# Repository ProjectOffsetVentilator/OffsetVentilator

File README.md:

# OffsetVentilator
Main code and documentation repository for the Helpful Engineering Offset Ventilator project.

## Google drive files
Original Proposal https://docs.google.com/document/d/1oH8tw4RyOXmuNEdUx4EB1WGNugmwalZ1q0ezBaePJMA/edit?usp=sharing

Intro Document https://docs.google.com/document/d/1AArDUr8NLNWiVp7JXv_tODoiIWyCNlN2cYjHagHkWg8/edit?usp=sharing

Rapidly Manufactured Ventilator Specs (MHRA) https://drive.google.com/file/d/1wRC2XBbxR0HcKKCPTSRZzICJgym3Go8j/view?usp=sharing

Minimal viable product https://drive.google.com/file/d/13SMGtRrQCkC2kCIZivcb2gAX9uvTnBLK/view?usp=sharing

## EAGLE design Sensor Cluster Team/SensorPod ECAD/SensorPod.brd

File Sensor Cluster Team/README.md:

# Sensor Cluster Team Readme

## Team Google files
Sensor spec sheet https://docs.google.com/spreadsheets/d/1ZPNHejLOZxX_iVy-8t1VuLuAKOtTS-A7I4RntlRBN0Y/edit?usp=sharing

## Useful links and resources
MVP specs https://drive.google.com/file/d/13SMGtRrQCkC2kCIZivcb2gAX9uvTnBLK/view?usp=sharing

Rapidly Manufactured Ventilator System specs (MHRA) https://drive.google.com/file/d/1wRC2XBbxR0HcKKCPTSRZzICJgym3Go8j/view?usp=sharing

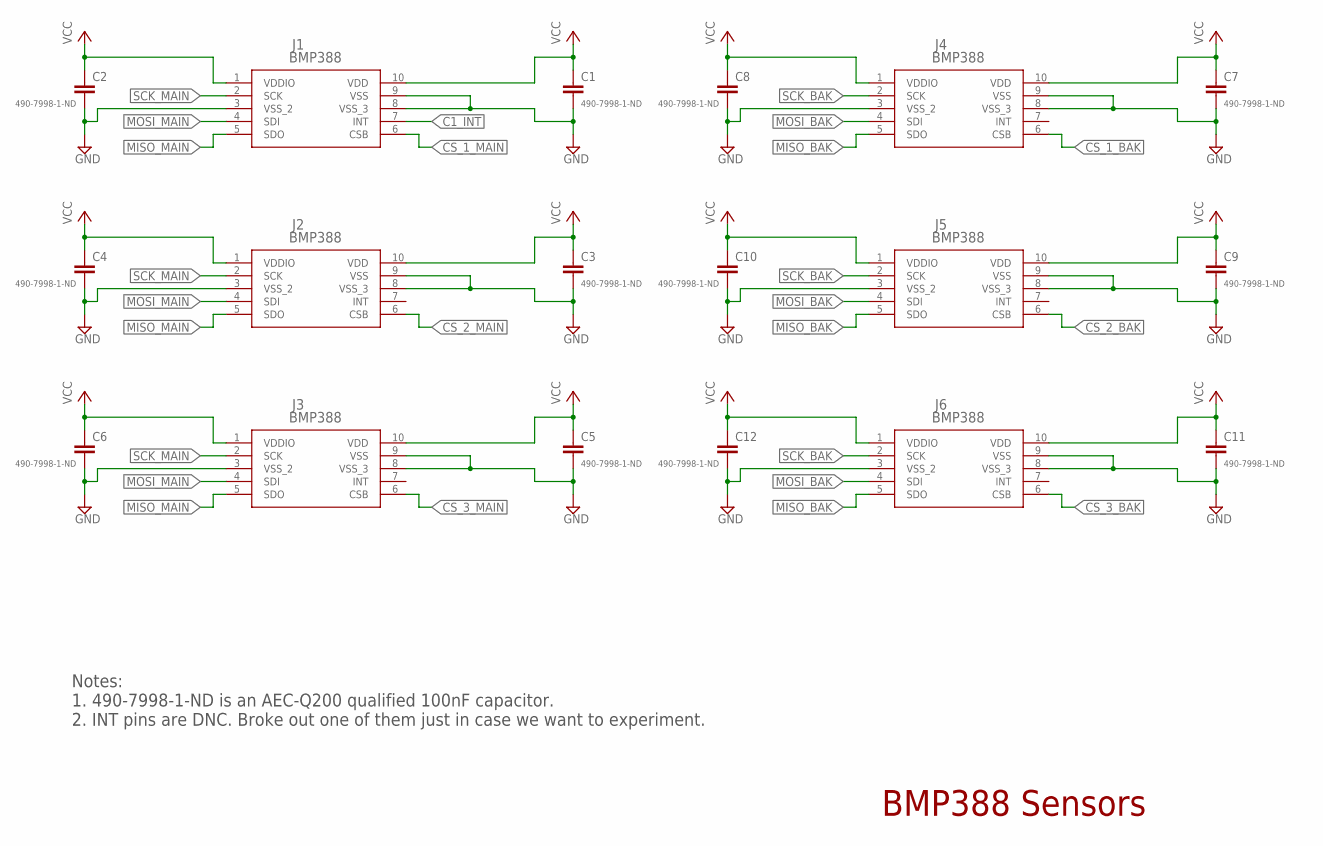
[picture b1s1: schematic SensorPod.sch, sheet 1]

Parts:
C1, C2, C3, C4, C5, C6, C7, C8, C9, C10, C11, C12: 490-7998-1-ND; C0402
J1, J2, J3, J4, J5, J6: BMP388; QFN_BMP388

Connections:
C1_INT: J1.7 (INT); also elsewhere on the board
CS_1_BAK: J4.6 (CSB); also elsewhere on the board
CS_1_MAIN: J1.6 (CSB); also elsewhere on the board
CS_2_BAK: J5.6 (CSB); also elsewhere on the board
CS_2_MAIN: J2.6 (CSB); also elsewhere on the board
CS_3_BAK: J6.6 (CSB); also elsewhere on the board
CS_3_MAIN: J3.6 (CSB); also elsewhere on the board
GND: C1.2, C2.2, C3.2, C4.2, C5.2, C6.2, C7.2, C8.2, C9.2, C10.2, C11.2, C12.2, J1.3 (VSS_2), J1.8 (VSS_3), J1.9 (VSS), J2.3 (VSS_2), J2.8 (VSS_3), J2.9 (VSS), J3.3 (VSS_2), J3.8 (VSS_3), J3.9 (VSS), J4.3 (VSS_2), J4.8 (VSS_3), J4.9 (VSS), J5.3 (VSS_2), J5.8 (VSS_3), J5.9 (VSS), J6.3 (VSS_2), J6.8 (VSS_3), J6.9 (VSS); also elsewhere on the board
MISO_BAK: J4.5 (SDO), J5.5 (SDO), J6.5 (SDO); also elsewhere on the board
MISO_MAIN: J1.5 (SDO), J2.5 (SDO), J3.5 (SDO); also elsewhere on the board
MOSI_BAK: J4.4 (SDI), J5.4 (SDI), J6.4 (SDI); also elsewhere on the board
MOSI_MAIN: J1.4 (SDI), J2.4 (SDI), J3.4 (SDI); also elsewhere on the board
SCK_BAK: J4.2 (SCK), J5.2 (SCK), J6.2 (SCK); also elsewhere on the board
SCK_MAIN: J1.2 (SCK), J2.2 (SCK), J3.2 (SCK); also elsewhere on the board
VCC: C1.1, C2.1, C3.1, C4.1, C5.1, C6.1, C7.1, C8.1, C9.1, C10.1, C11.1, C12.1, J1.1 (VDDIO), J1.10 (VDD), J2.1 (VDDIO), J2.10 (VDD), J3.1 (VDDIO), J3.10 (VDD), J4.1 (VDDIO), J4.10 (VDD), J5.1 (VDDIO), J5.10 (VDD), J6.1 (VDDIO), J6.10 (VDD); also elsewhere on the board

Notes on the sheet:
Notes: 1. 490-7998-1-ND is an AEC-Q200 qualified 100nF capacitor. 2. INT pins are DNC. Broke out one of them just in case we want to experiment.
BMP388 Sensors

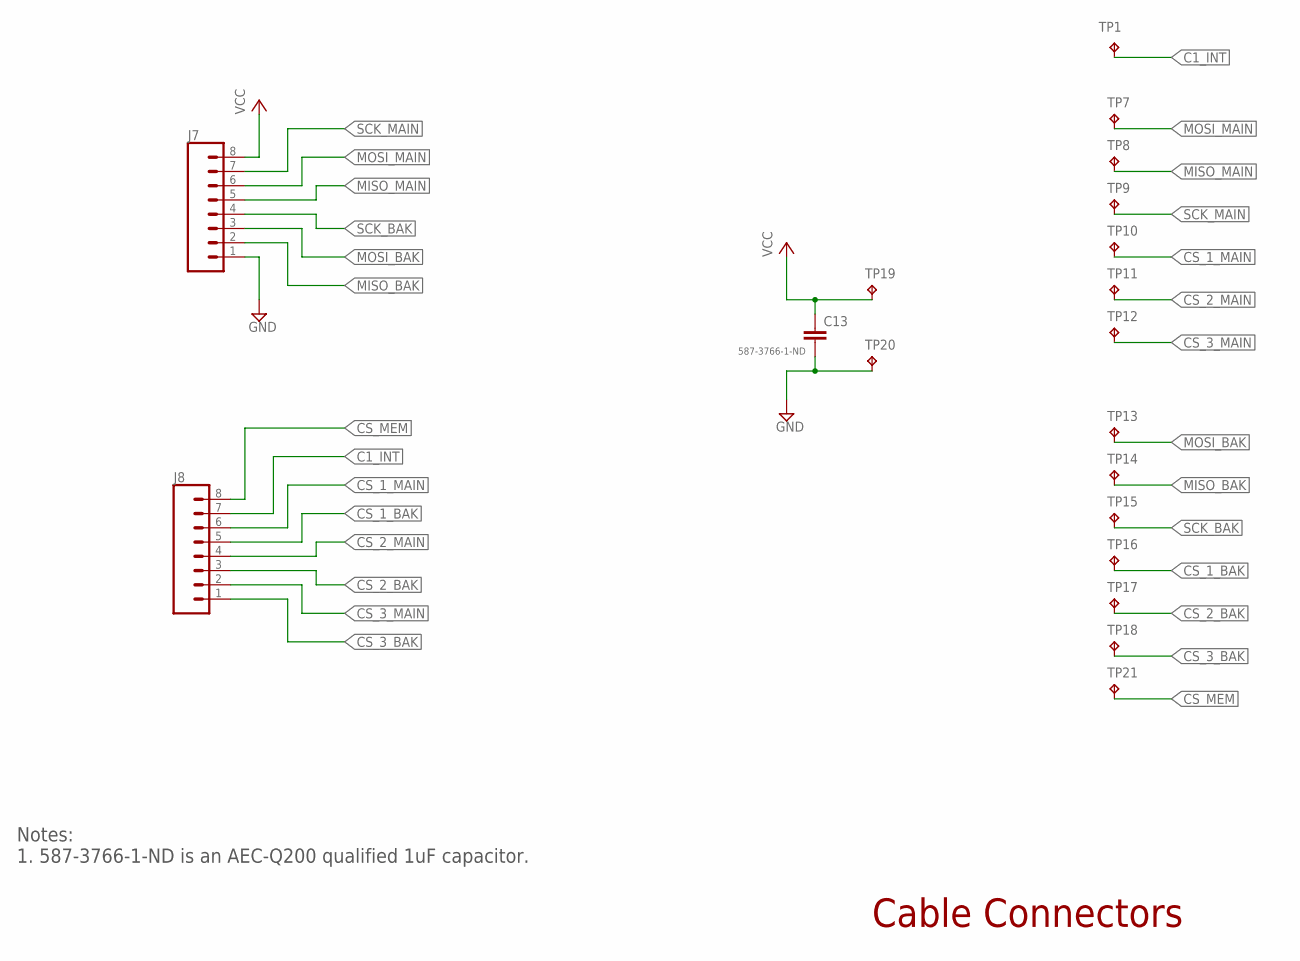
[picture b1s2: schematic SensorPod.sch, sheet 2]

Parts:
C13: 587-3766-1-ND; C0402
J7, J8: CONN_08"; 1X08
TP1, TP7, TP8, TP9, TP10, TP11, TP12, TP13, TP14, TP15, TP16, TP17, TP18, TP19, TP20, TP21: TPB1,27; B1,27

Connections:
C1_INT: J8.7, TP1.TP; also elsewhere on the board
CS_1_BAK: J8.5, TP16.TP; also elsewhere on the board
CS_1_MAIN: J8.6, TP10.TP; also elsewhere on the board
CS_2_BAK: J8.3, TP17.TP; also elsewhere on the board
CS_2_MAIN: J8.4, TP11.TP; also elsewhere on the board
CS_3_BAK: J8.1, TP18.TP; also elsewhere on the board
CS_3_MAIN: J8.2, TP12.TP; also elsewhere on the board
CS_MEM: J8.8, TP21.TP; also elsewhere on the board
GND: C13.2, J7.1, TP20.TP; also elsewhere on the board
MISO_BAK: J7.2, TP14.TP; also elsewhere on the board
MISO_MAIN: J7.5, TP8.TP; also elsewhere on the board
MOSI_BAK: J7.3, TP13.TP; also elsewhere on the board
MOSI_MAIN: J7.6, TP7.TP; also elsewhere on the board
SCK_BAK: J7.4, TP15.TP; also elsewhere on the board
SCK_MAIN: J7.7, TP9.TP; also elsewhere on the board
VCC: C13.1, J7.8, TP19.TP; also elsewhere on the board

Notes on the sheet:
Cable Connectors
Notes: 1. 587-3766-1-ND is an AEC-Q200 qualified 1uF capacitor.

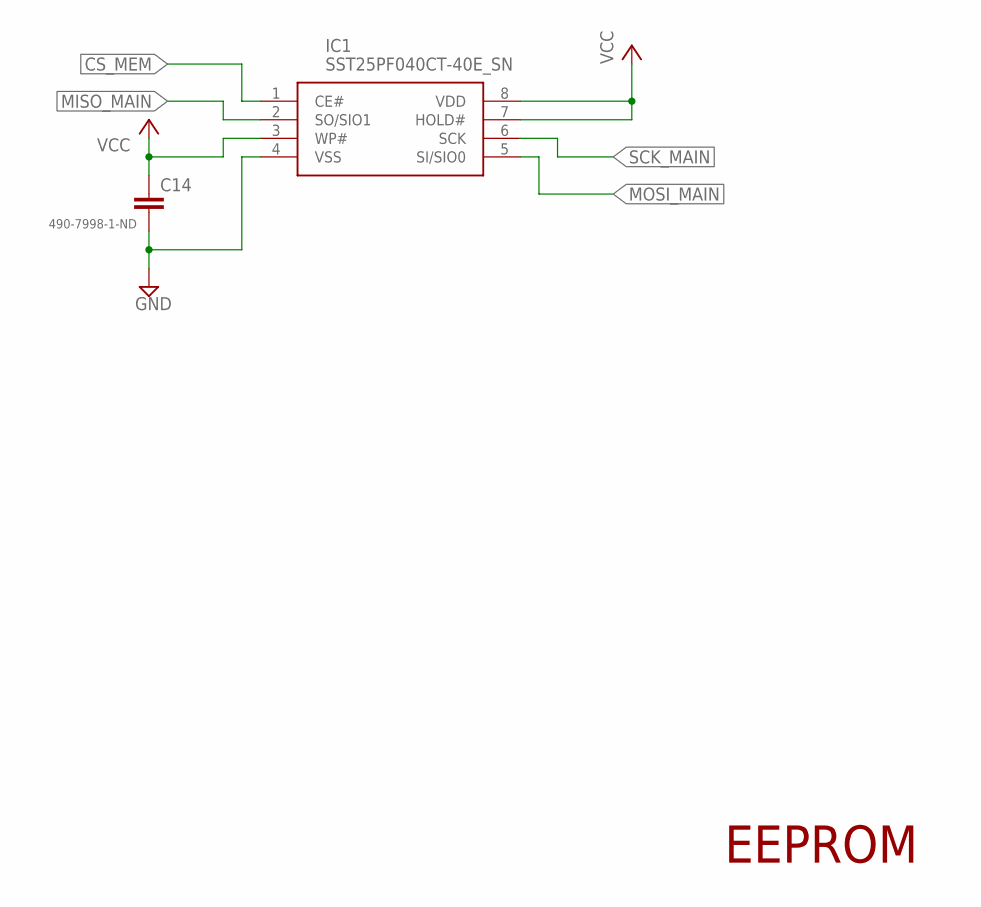
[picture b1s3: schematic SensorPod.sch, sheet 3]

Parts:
C14: 490-7998-1-ND; C0402
IC1: SST25PF040CT-40E_SN; SOIC127P600X175-8N

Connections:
CS_MEM: IC1.1 (CE#); also elsewhere on the board
GND: C14.2, IC1.4 (VSS); also elsewhere on the board
MISO_MAIN: IC1.2 (SO/SIO1); also elsewhere on the board
MOSI_MAIN: IC1.5 (SI/SIO0); also elsewhere on the board
SCK_MAIN: IC1.6 (SCK); also elsewhere on the board
VCC: C14.1, IC1.3 (WP#), IC1.7 (HOLD#), IC1.8 (VDD); also elsewhere on the board

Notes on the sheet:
EEPROM

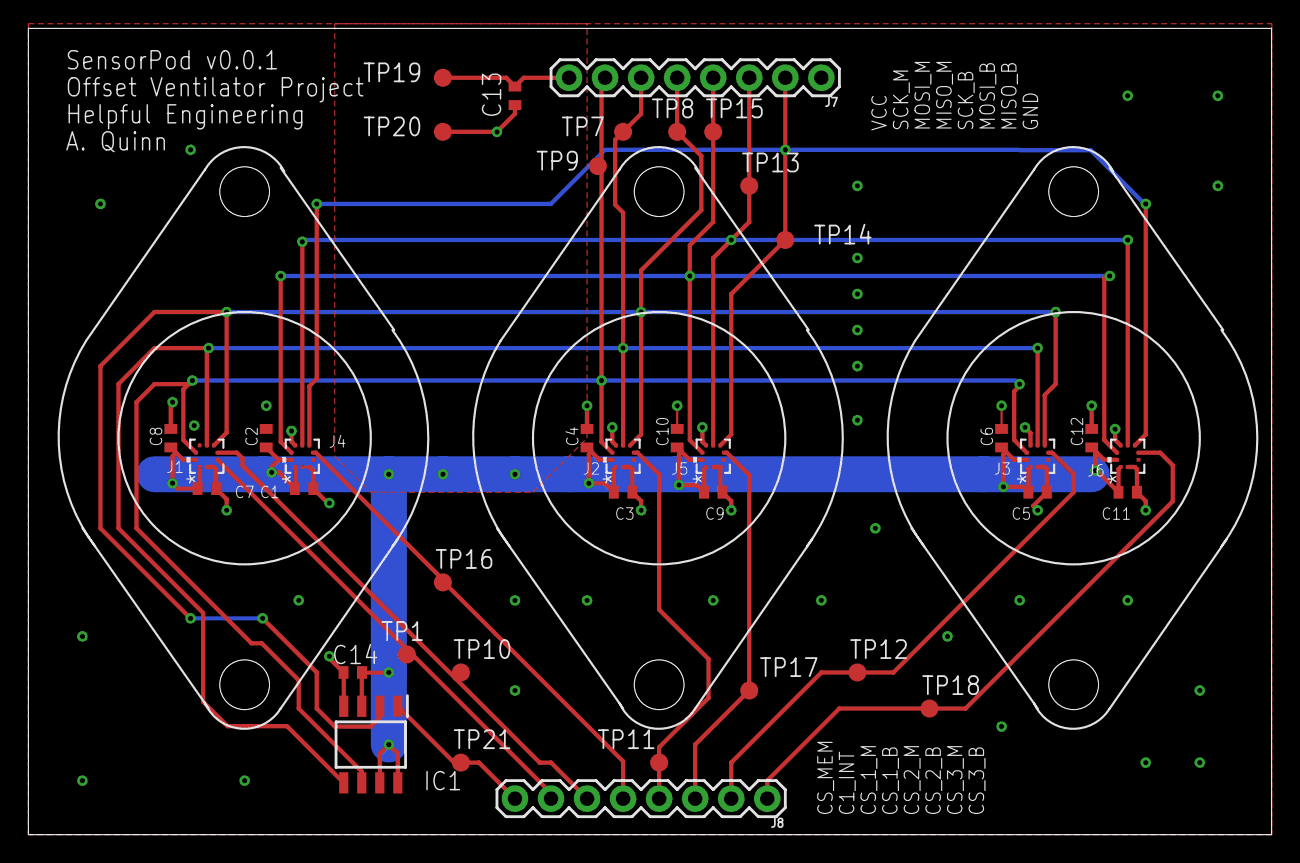
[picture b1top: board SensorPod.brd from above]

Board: 2 copper layers, 87.6 x 56.8 mm, 39 parts (0 on the bottom side), 16 nets.

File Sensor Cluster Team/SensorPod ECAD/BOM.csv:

Designator,Value,Digikey Part Number,Package
C1,100nF,490-7998-1-ND,C0402
C2,100nF,490-7998-1-ND,C0402
C3,100nF,490-7998-1-ND,C0402
C4,100nF,490-7998-1-ND,C0402
C5,100nF,490-7998-1-ND,C0402
C6,100nF,490-7998-1-ND,C0402
C7,100nF,490-7998-1-ND,C0402
C8,100nF,490-7998-1-ND,C0402
C9,100nF,490-7998-1-ND,C0402
C10,100nF,490-7998-1-ND,C0402
C11,100nF,490-7998-1-ND,C0402
C12,100nF,490-7998-1-ND,C0402
C13,1uF,587-3766-1-ND,C0402
C14,100nF,490-7998-1-ND,C0402
IC1,SST25PF040CT-40E_SN,SST25PF040CT-40E/SNCT-ND,
J1,BMP388,828-1079-1-ND,
J2,BMP388,828-1079-1-ND,
J3,BMP388,828-1079-1-ND,
J4,BMP388,828-1079-1-ND,
J5,BMP388,828-1079-1-ND,
J6,BMP388,828-1079-1-ND,

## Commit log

2020-03-23 Added CERN License
2020-03-23 Added Electrical Requirements Matrix
2020-03-23 XLSX Diff Test
2020-03-23 Added Spec Sheet + Preliminary Trade Study
2020-03-23 Create readme.txt
    Initial commit.
2020-03-23 Add files via upload
    Initial commit
2020-03-23 Updated readme to include links to project google drive files
2020-03-23 Added a link to the MVP doc
2020-03-24 Added sensor team folder & Readme
2020-03-25 Created Software team folder
    Also added README
2020-03-26 Added CodeFramework.md
2020-03-26 Made minor updates to codeframework.md
2020-03-26 Added a project directory for new members
    This will help new members find who to contact to get started
2020-03-26 Added resources to learning section
2020-03-26 Move license from readme to license file
2020-03-26 License is now in it's own file
2020-03-26 removed redundant license
2020-03-26 update title of readme
2020-03-27 Reorganized Files
2020-03-27 Updated ElectricalReqMat to include more display and alarm buzzer options.
2020-03-27 Added link to blink without delay sketch
2020-03-27 Major Updates to CodeFramework.md
2020-03-28 Added Sensor Pod ECAD (in progress)
2020-03-28 Added MPXC2011DT1 to sensor list.
2020-03-30 Deleted codeframwork.md
    Currently working on a code specs document to replace it
2020-03-30 Added link to code specs draft
2020-03-31 Create MotorResearch
2020-03-31 Initial files for motor search
    Setting up files
2020-03-31 HW architecture diagram (Pictures and source doc)
2020-04-02 v0_0_1 Sensor Pod Finished
2020-04-03 Initial version of ventsense sensor data capture app.
    ventsense_fw v0.1-0
    ventsense_client v0.1-0
2020-04-04 Added BOM and Gerber files
2020-04-04 Updated ventsense_client to support Python 3 and Windows.
2020-04-04 Added executable for Windows.
2020-04-05 Added prebuilt ventsense client executable for Linux.
2020-04-05 Fixed compatibility issue with ventsense_client. Added comments.
2020-04-05 Fixed ventsense_client bug and updated linux binary.
2020-04-05 Fixed more compatibility issues with ventsense_client.
2020-04-05 Updated ventsense_client binaries.
2020-04-06 Updated comments and readme's.
2020-04-06 Removed the draft status on the MVP document
2020-04-06 Fixed README formatting
2020-04-06 Updated HW architecture files
2020-04-07 Deleted Directory.md
    Not a useful resource for new members because the swam approach makes it hard to maintain
2020-04-07 Removed servo resources on software README
2020-04-08 Updated ventsense to support 3 sensors. Fixed several serial port issues.
2020-04-08 Updated ventsense_client version number.
2020-04-11 Updates to HW architecture files
2020-04-11 Initial implementation of plotting feature in ventsense client.
2020-04-13 Added support for plotting 3 pressure sensors to ventsense.
2020-04-14 software util in Processing creating a csv table and simple plotting
2020-04-14 Added temperature plots and labels to ventsense_client.
2020-04-15 Fixed character encoding issue in ventsense_client.
2020-04-15 Added ability to save/load config params in ventsense client. Added additional command line options for customizeability.
2020-04-15 Added features to allow the user to enable/disable the graphical plot, set range of x/y axes, plot relative values, and select between hPa and cmH2O for units.
2020-04-15 Updated ventsense client help text. Minor refactorings.
2020-04-15 Updated ventsense client executables.
2020-04-15 Added combined plot support to ventsense client.
2020-04-15 Added legend when combining plots in ventsense client.
2020-04-16 Added option to autoscale the Y axis in ventsense client.
2020-04-16 Made ventsens client's Y autoscale feature a little smarter, to improve usability and animation quality.
2020-04-16 Minor ventsense client bug fixes.
2020-04-16 Released v0.2-2 of ventsense client. Supports customizeable realtime graphical plots. Updated ventsense client executables.
2020-04-17 Added documentation for ventsense client. Fixed minor bug in command-line arguments.
2020-04-24 V1 of HW Architecture!
2020-04-24 added motor_bringup folder.
2020-04-24 Added wiring diagram for the prototype.
2020-04-25 Fixed issue with prototype wiring diagram (GND and VCC were switched on motor).
2020-05-09 added ventesense_fw_flowCalc with the code organised in classes
2020-05-28 Added fisrt draft of control software
2020-05-28 added gitignore
2020-05-28 switched folders

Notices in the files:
parts and their libraries:
SparkFun-Connectors: Licensing: Creative Commons ShareAlike 4.0 International - https://creativecommons.org/licenses/by-sa/4.0
COPYRIGHT: Copyright (C) 2018 Accelerated Designs. All rights reserved
